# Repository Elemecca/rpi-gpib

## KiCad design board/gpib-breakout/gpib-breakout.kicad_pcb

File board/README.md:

## Copying

Copyright 2019 Sam Hanes

This documentation describes Open Hardware and is licensed under
the CERN Open Hardware License v1.2.

You may redistribute and modify this documentation under the terms of
the CERN OHL v1.2. (http://ohwr.org/cernohl). This documentation is
distributed WITHOUT ANY EXPRESS OR IMPLIED WARRANTY, INCLUDING OF
MERCHANTABILITY, SATISFACTORY QUALITY AND FITNESS FOR APARTICULAR
PURPOSE. Please see the CERN OHL v1.2 for applicable conditions

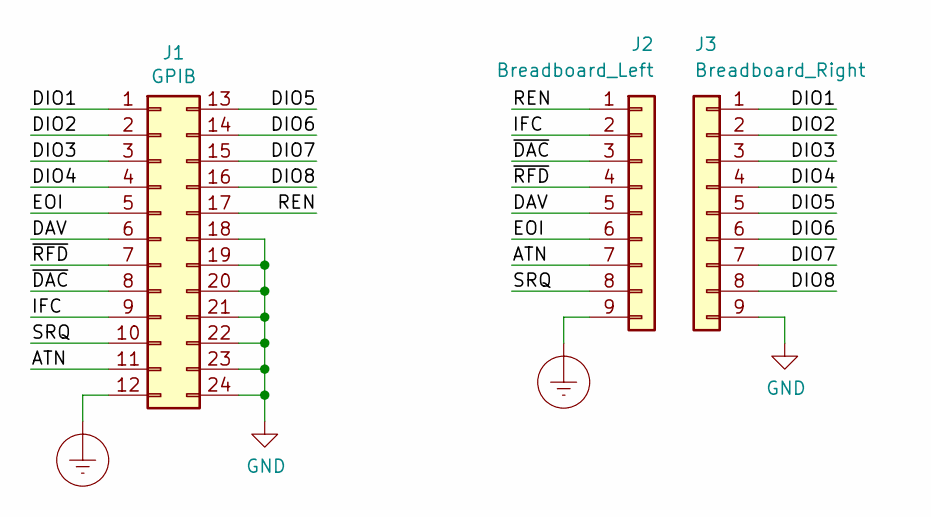
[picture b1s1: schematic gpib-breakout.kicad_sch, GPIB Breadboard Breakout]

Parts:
J1: GPIB; NorComp_111-024-213L001
J2: Breadboard_Left; PinHeader_1x09_P2.54mm_Vertical
J3: Breadboard_Right; PinHeader_1x09_P2.54mm_Vertical

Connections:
/ATN: J1.11, J2.7
/DAV: J1.6, J2.5
/DIO1: J1.1, J3.1
/DIO2: J1.2, J3.2
/DIO3: J1.3, J3.3
/DIO4: J1.4, J3.4
/DIO5: J1.13, J3.5
/DIO6: J1.14, J3.6
/DIO7: J1.15, J3.7
/DIO8: J1.16, J3.8
/EOI: J1.5, J2.6
/IFC: J1.9, J2.2
/REN: J1.17, J2.1
/SRQ: J1.10, J2.8
/~DAC: J1.8, J2.3
/~RFD: J1.7, J2.4
Earth_Protective: J1.12, J2.9
GND: J1.18, J1.19, J1.20, J1.21, J1.22, J1.23, J1.24, J3.9

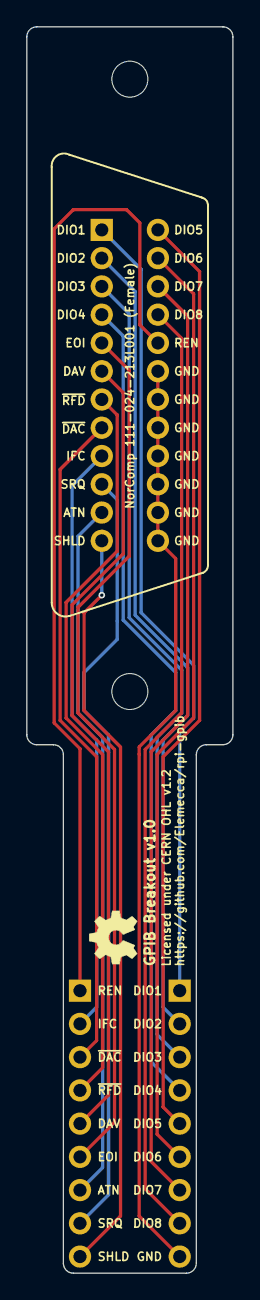
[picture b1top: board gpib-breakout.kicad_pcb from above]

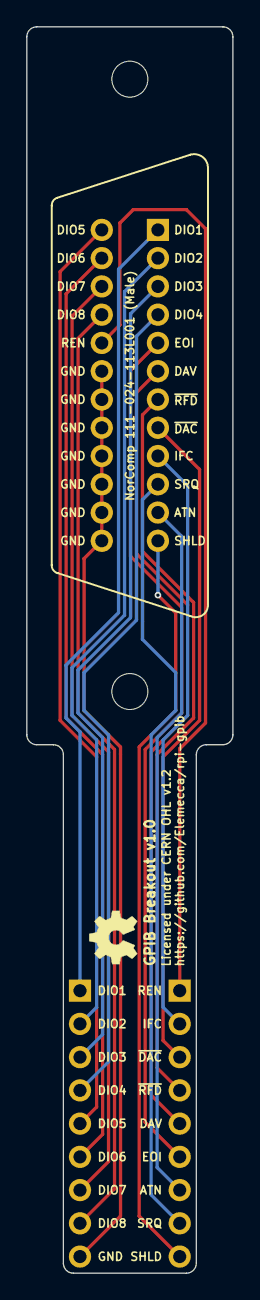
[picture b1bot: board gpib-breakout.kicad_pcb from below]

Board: 2 copper layers, 15.7 x 95.2 mm, 5 parts (3 on the bottom side), 18 nets.

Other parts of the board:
OSHW: LOGO; OSHW
OSHW#2: LOGO; OSHW

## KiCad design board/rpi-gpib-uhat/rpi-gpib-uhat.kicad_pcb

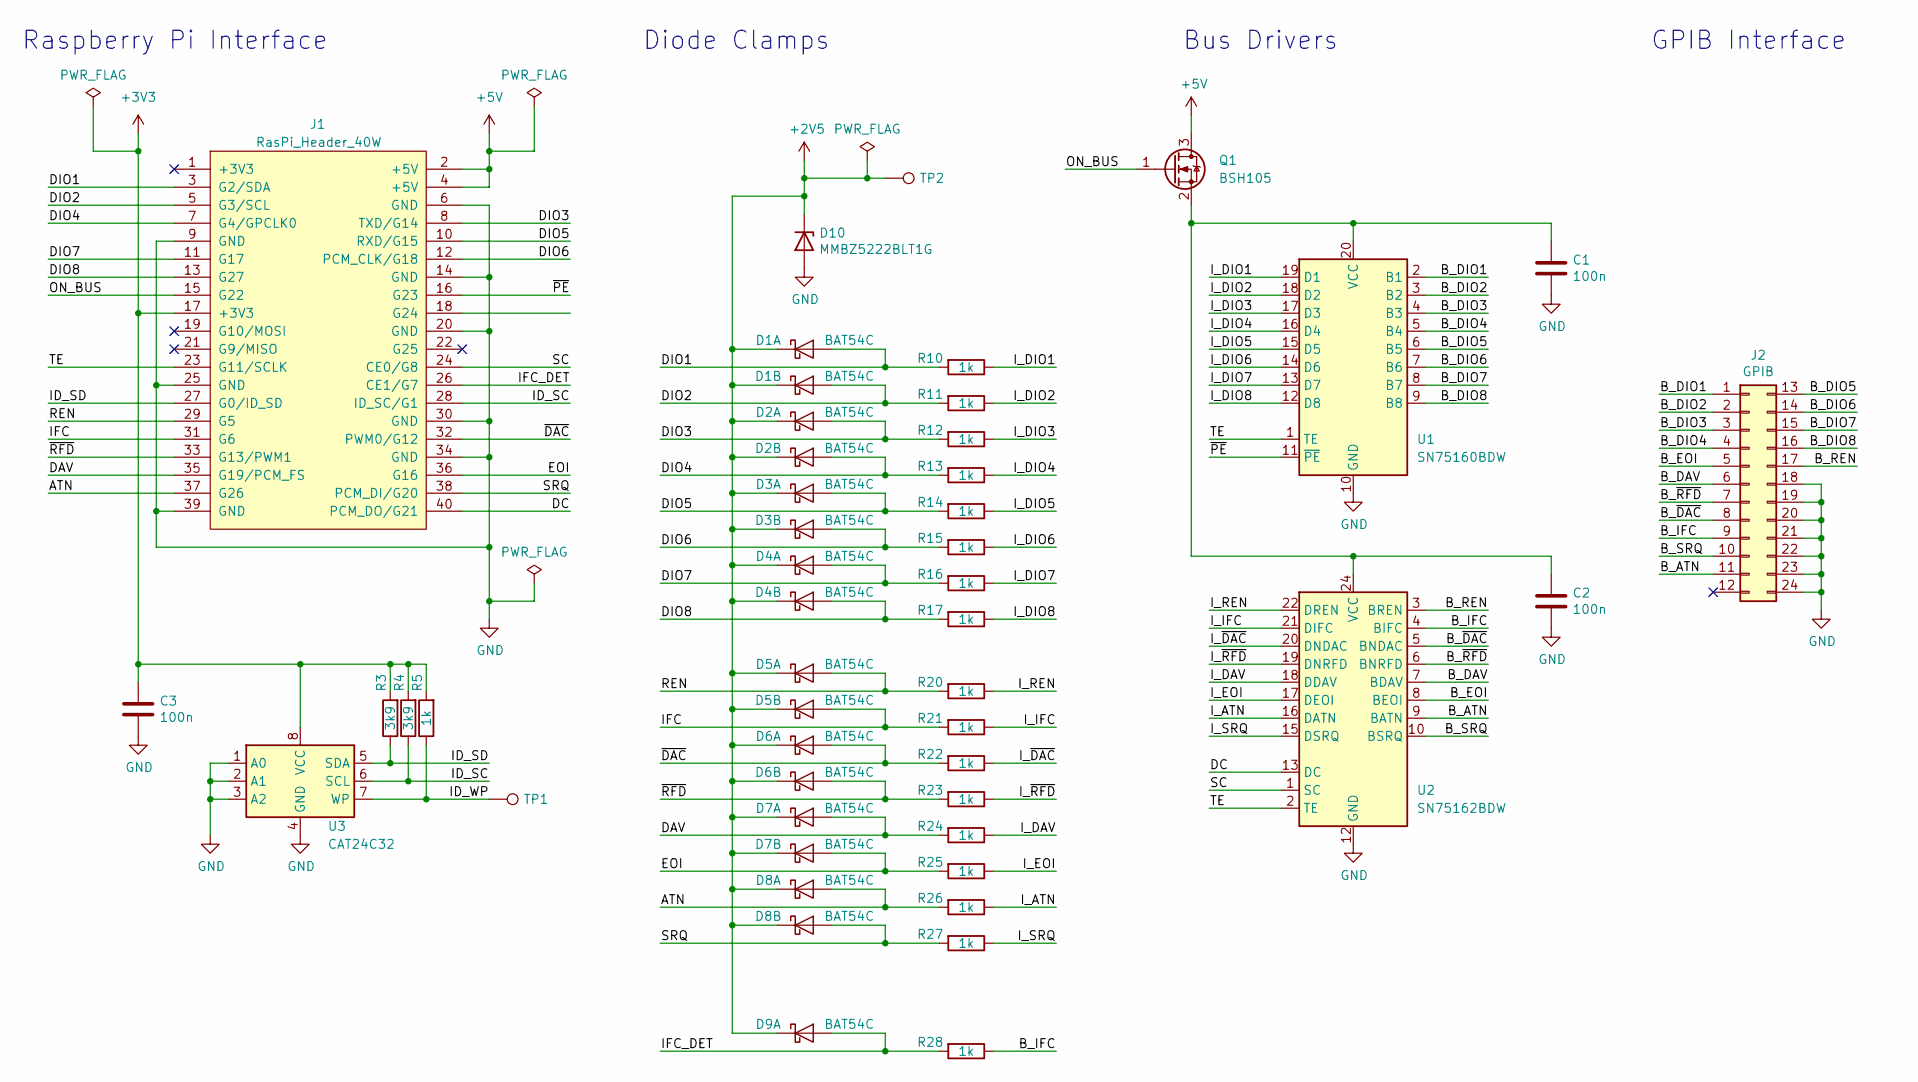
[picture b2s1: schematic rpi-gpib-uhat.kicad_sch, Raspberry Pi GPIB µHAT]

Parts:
C1, C2, C3: 100n; C_0402_1005Metric
D1, D2, D3, D4, D5, D6, D7, D8, D9: BAT54C; SOT-23
D10: MMBZ5222BLT1G; SC-59
J1: RasPi_Header_40W; PinSocket_2x20_P2.54mm_Vertical_Centered_Anchor
J2: GPIB; NorComp_111-024-113L001_NoScrews
Q1: BSH105; SOT-23
R3, R4: 3k9; R_0402_1005Metric
R5, R10, R11, R12, R13, R14, R15, R16, R17, R20, R21, R22, R23, R24, R25, R26, R27, R28: 1k; R_0402_1005Metric
TP1, TP2: TestPoint; TestPoint_Pad_D1.0mm
U1: SN75160BDW; SOIC-20W_7.5x12.8mm_P1.27mm
U2: SN75162BDW; SOIC-24W_7.5x15.4mm_P1.27mm
U3: CAT24C32; SOIC-8_3.9x4.9mm_P1.27mm

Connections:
+2V5: D1.3 (K), D2.3 (K), D3.3 (K), D4.3 (K), D5.3 (K), D6.3 (K), D7.3 (K), D8.3 (K), D9.3 (K), D10.1 (K), TP2.1
+3V3: C3.1, J1.17 (+3V3), R3.2, R4.2, R5.2, U3.8 (VCC)
+5V: J1.2 (+5V), J1.4 (+5V), Q1.3 (D)
/ATN: D8.1 (A), J1.37 (G26), R26.2
/B_ATN: J2.11, U2.9 (BATN)
/B_DAV: J2.6, U2.7 (BDAV)
/B_DIO1: J2.1, U1.2 (B1)
/B_DIO2: J2.2, U1.3 (B2)
/B_DIO3: J2.3, U1.4 (B3)
/B_DIO4: J2.4, U1.5 (B4)
/B_DIO5: J2.13, U1.6 (B5)
/B_DIO6: J2.14, U1.7 (B6)
/B_DIO7: J2.15, U1.8 (B7)
/B_DIO8: J2.16, U1.9 (B8)
/B_EOI: J2.5, U2.8 (BEOI)
/B_IFC: J2.9, R28.1, U2.4 (BIFC)
/B_REN: J2.17, U2.3 (BREN)
/B_SRQ: J2.10, U2.10 (BSRQ)
/B_~DAC: J2.8, U2.5 (BNDAC)
/B_~RFD: J2.7, U2.6 (BNRFD)
/DAV: D7.1 (A), J1.35 (G19/PCM_FS), R24.2
/DC: J1.40 (PCM_DO/G21), U2.13 (DC)
/DIO1: D1.1 (A), J1.3 (G2/SDA), R10.2
/DIO2: D1.2 (A), J1.5 (G3/SCL), R11.2
/DIO3: D2.1 (A), J1.8 (TXD/G14), R12.2
/DIO4: D2.2 (A), J1.7 (G4/GPCLK0), R13.2
/DIO5: D3.1 (A), J1.10 (RXD/G15), R14.2
/DIO6: D3.2 (A), J1.12 (PCM_CLK/G18), R15.2
/DIO7: D4.1 (A), J1.11 (G17), R16.2
/DIO8: D4.2 (A), J1.13 (G27), R17.2
/EOI: D7.2 (A), J1.36 (G16), R25.2
/ID_SC: J1.28 (ID_SC/G1), R4.1, U3.6 (SCL)
/ID_SD: J1.27 (G0/ID_SD), R3.1, U3.5 (SDA)
/ID_WP: R5.1, TP1.1, U3.7 (WP)
/IFC: D5.2 (A), J1.31 (G6), R21.2
/IFC_DET: D9.1 (A), J1.26 (CE1/G7), R28.2
/I_ATN: R26.1, U2.16 (DATN)
/I_DAV: R24.1, U2.18 (DDAV)
/I_DIO1: R10.1, U1.19 (D1)
/I_DIO2: R11.1, U1.18 (D2)
/I_DIO3: R12.1, U1.17 (D3)
/I_DIO4: R13.1, U1.16 (D4)
/I_DIO5: R14.1, U1.15 (D5)
/I_DIO6: R15.1, U1.14 (D6)
/I_DIO7: R16.1, U1.13 (D7)
/I_DIO8: R17.1, U1.12 (D8)
/I_EOI: R25.1, U2.17 (DEOI)
/I_IFC: R21.1, U2.21 (DIFC)
/I_REN: R20.1, U2.22 (DREN)
/I_SRQ: R27.1, U2.15 (DSRQ)
/I_~DAC: R22.1, U2.20 (DNDAC)
/I_~RFD: R23.1, U2.19 (DNRFD)
/ON_BUS: J1.15 (G22), Q1.1 (G)
/REN: D5.1 (A), J1.29 (G5), R20.2
/SC: J1.24 (CE0/G8), U2.1 (SC)
/SRQ: D8.2 (A), J1.38 (PCM_DI/G20), R27.2
/TE: J1.23 (G11/SCLK), U1.1 (TE), U2.2 (TE)
/~DAC: D6.1 (A), J1.32 (PWM0/G12), R22.2
/~PE: J1.16 (G23), U1.11 (~PE)
/~RFD: D6.2 (A), J1.33 (G13/PWM1), R23.2
GND: C1.2, C2.2, C3.2, D10.2 (A), J1.6 (GND), J1.9 (GND), J1.14 (GND), J1.20 (GND), J1.25 (GND), J1.30 (GND), J1.34 (GND), J1.39 (GND), J2.18, J2.19, J2.20, J2.21, J2.22, J2.23, J2.24, U1.10 (GND), U2.12 (GND), U3.1 (A0), U3.2 (A1), U3.3 (A2), U3.4 (GND)
unnamed: C1.1, C2.1, Q1.2 (S), U1.20 (VCC), U2.24 (VCC)

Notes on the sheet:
Bus Drivers
Raspberry Pi Interface
Diode Clamps
GPIB Interface

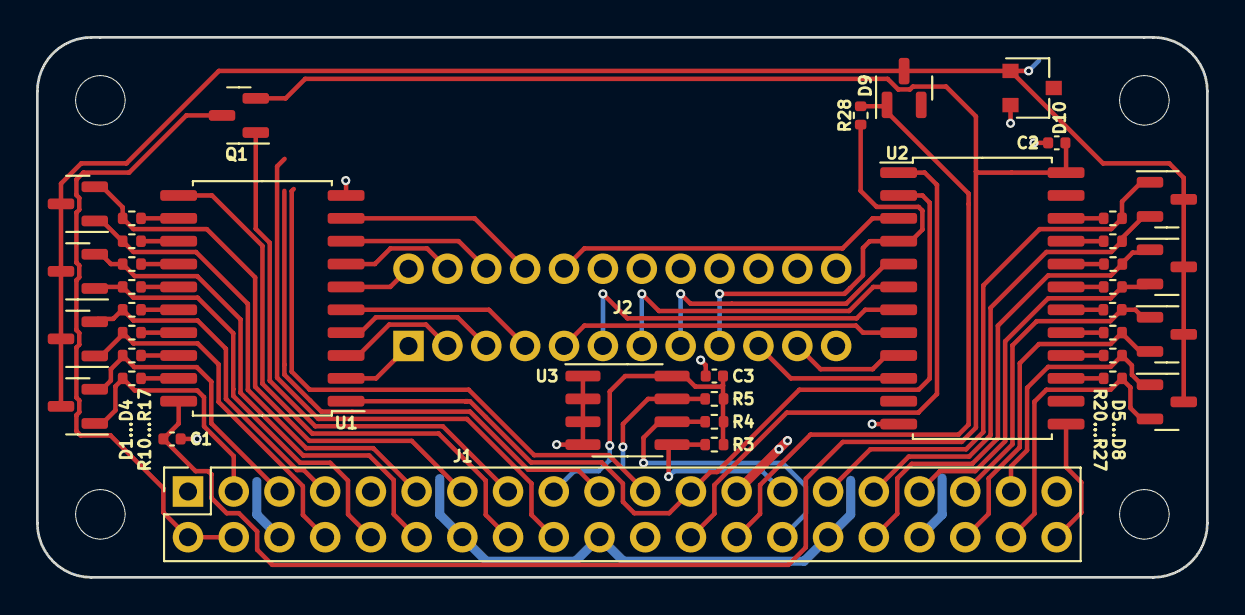
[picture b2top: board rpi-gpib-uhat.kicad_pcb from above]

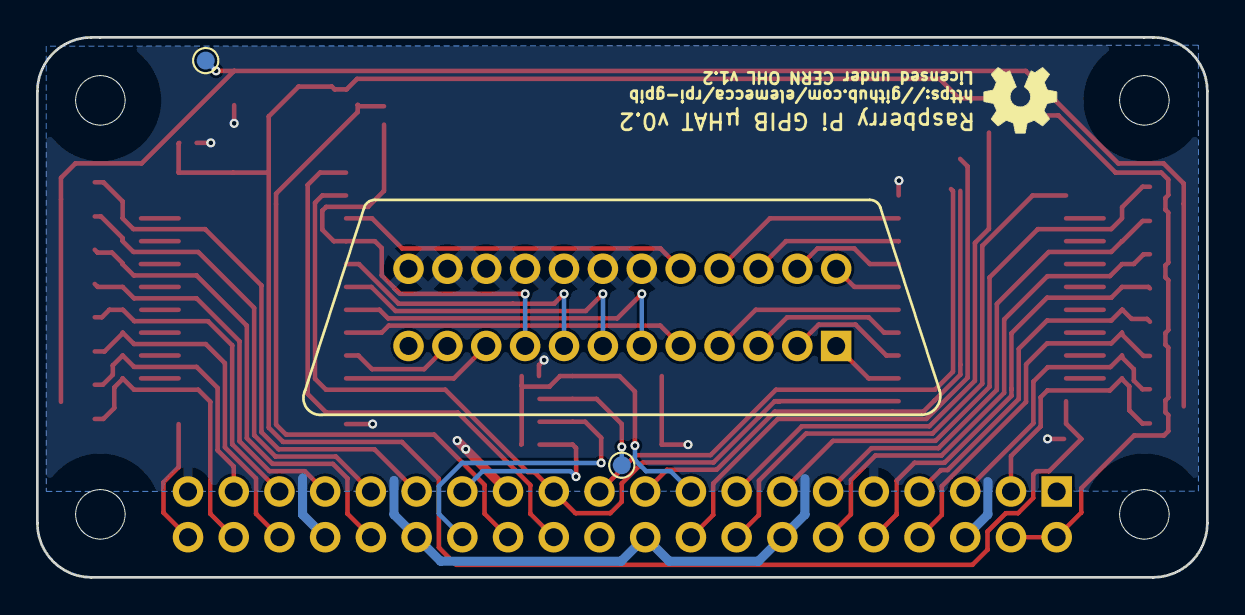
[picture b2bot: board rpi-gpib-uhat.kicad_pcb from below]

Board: 2 copper layers, 65.0 x 30.0 mm, 46 parts (4 on the bottom side), 62 nets.

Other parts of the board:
H1, H2, H3, H4: MountingHole; MountingHole_RPi_HAT
OSHW: LOGO; OSHW

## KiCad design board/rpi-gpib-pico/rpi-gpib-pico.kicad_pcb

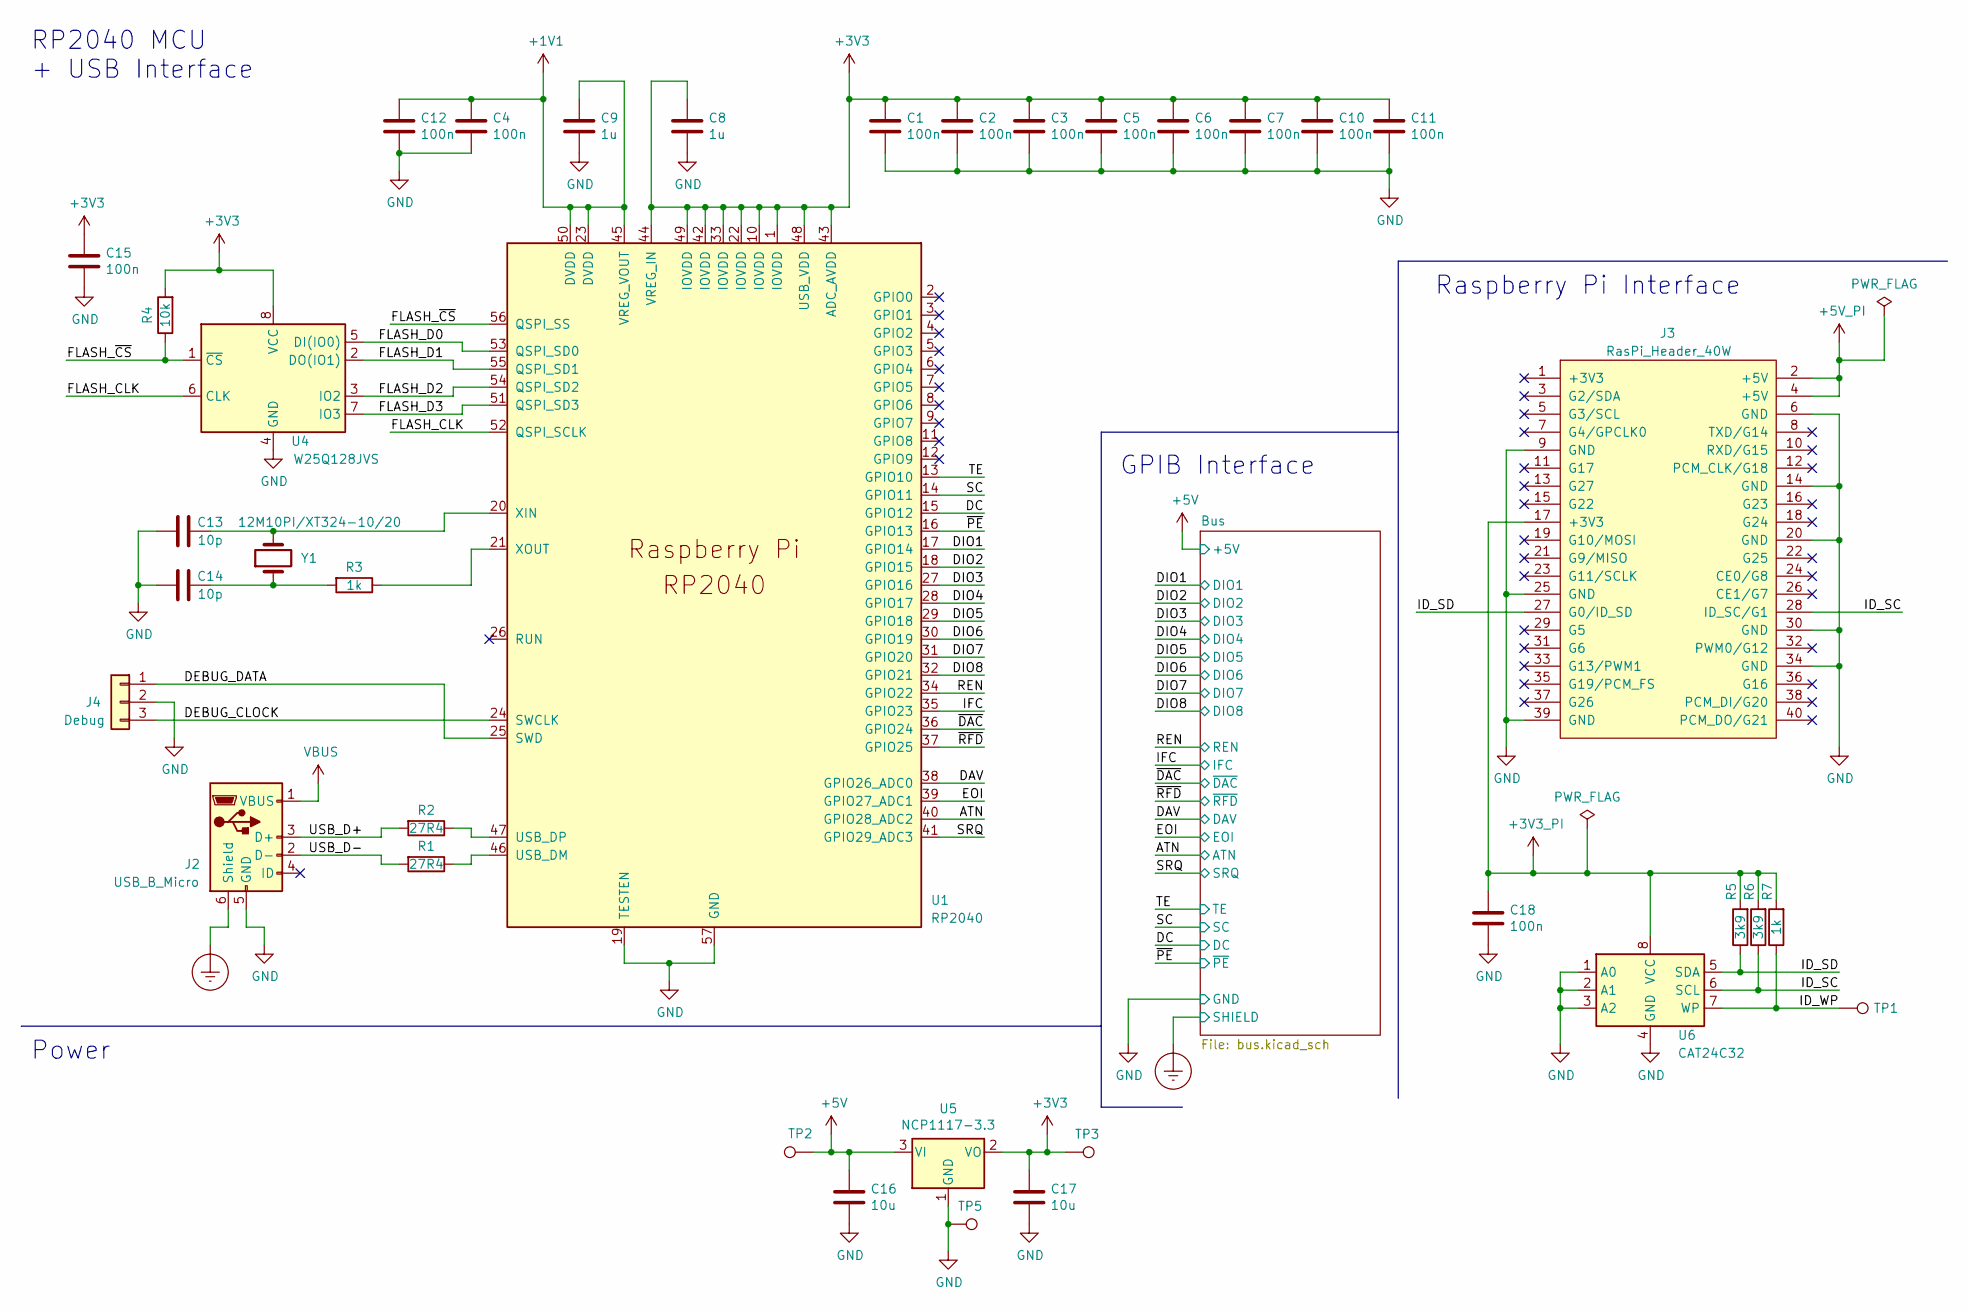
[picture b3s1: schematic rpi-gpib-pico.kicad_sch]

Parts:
C1, C2, C3, C4, C5, C6, C7, C10, C11, C12, C15, C18: 100n; C_0402_1005Metric
C8, C9: 1u; C_0402_1005Metric
C13, C14: 10p; C_0402_1005Metric
C16, C17: 10u; C_0402_1005Metric
J2: USB_B_Micro; USB_Micro-B_Amphenol_10118194_Horizontal
J3: RasPi_Header_40W; PinSocket_2x20_P2.54mm_Vertical_Centered_Anchor
J4: Debug; PinHeader_1x03_P2.54mm_Vertical
R1, R2: 27R4; R_0402_1005Metric
R3, R7: 1k; R_0402_1005Metric
R4: 10k; R_0402_1005Metric
R5, R6: 3k9; R_0402_1005Metric
TP1, TP2, TP3, TP5: TestPoint; TestPoint_Pad_D1.0mm
U1: RP2040; RP2040-QFN-56
U4: W25Q128JVS; SOIC-8_5.23x5.23mm_P1.27mm
U5: NCP1117-3.3; SOT-223-3_TabPin2
U6: CAT24C32; SOIC-8_3.9x4.9mm_P1.27mm
Y1: 12M10PI/XT324-10/20; Crystal_SMD_3225-4Pin_3.2x2.5mm

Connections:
+1V1: C4.1, C9.1, C12.1, U1.23 (DVDD), U1.45 (VREG_VOUT), U1.50 (DVDD)
+3V3: C1.1, C2.1, C3.1, C5.1, C6.1, C7.1, C8.1, C10.1, C11.1, C15.1, C17.1, R4.2, TP3.1, U1.1 (IOVDD), U1.10 (IOVDD), U1.22 (IOVDD), U1.33 (IOVDD), U1.42 (IOVDD), U1.43 (ADC_AVDD), U1.44 (VREG_IN), U1.48 (USB_VDD), U1.49 (IOVDD), U4.8 (VCC), U5.2 (VO)
+3V3_PI: C18.1, J3.17 (+3V3), R5.2, R6.2, R7.2, U6.8 (VCC)
+5V: C16.1, TP2.1, U5.3 (VI); also elsewhere on the board
+5V_PI: J3.2 (+5V), J3.4 (+5V)
/ATN: U1.40 (GPIO28_ADC2); also elsewhere on the board
/DAV: U1.38 (GPIO26_ADC0); also elsewhere on the board
/DC: U1.15 (GPIO12); also elsewhere on the board
/DEBUG_CLOCK: J4.3, U1.24 (SWCLK)
/DEBUG_DATA: J4.1, U1.25 (SWD)
/DIO1: U1.17 (GPIO14); also elsewhere on the board
/DIO2: U1.18 (GPIO15); also elsewhere on the board
/DIO3: U1.27 (GPIO16); also elsewhere on the board
/DIO4: U1.28 (GPIO17); also elsewhere on the board
/DIO5: U1.29 (GPIO18); also elsewhere on the board
/DIO6: U1.30 (GPIO19); also elsewhere on the board
/DIO7: U1.31 (GPIO20); also elsewhere on the board
/DIO8: U1.32 (GPIO21); also elsewhere on the board
/EOI: U1.39 (GPIO27_ADC1); also elsewhere on the board
/FLASH_CLK: U1.52 (QSPI_SCLK), U4.6 (CLK)
/FLASH_D0: U1.53 (QSPI_SD0), U4.5 (DI(IO0))
/FLASH_D1: U1.55 (QSPI_SD1), U4.2 (DO(IO1))
/FLASH_D2: U1.54 (QSPI_SD2), U4.3 (IO2)
/FLASH_D3: U1.51 (QSPI_SD3), U4.7 (IO3)
/FLASH_~CS: R4.1, U1.56 (QSPI_SS), U4.1 (~CS)
/ID_SC: J3.28 (ID_SC/G1), R6.1, U6.6 (SCL)
/ID_SD: J3.27 (G0/ID_SD), R5.1, U6.5 (SDA)
/ID_WP: R7.1, TP1.1, U6.7 (WP)
/IFC: U1.35 (GPIO23); also elsewhere on the board
/REN: U1.34 (GPIO22); also elsewhere on the board
/SC: U1.14 (GPIO11); also elsewhere on the board
/SRQ: U1.41 (GPIO29_ADC3); also elsewhere on the board
/TE: U1.13 (GPIO10); also elsewhere on the board
/USB_D+: J2.3 (D+), R2.2
/USB_D-: J2.2 (D-), R1.2
/~DAC: U1.36 (GPIO24); also elsewhere on the board
/~PE: U1.16 (GPIO13); also elsewhere on the board
/~RFD: U1.37 (GPIO25); also elsewhere on the board
Earth_Protective: J2.6 (Shield); also elsewhere on the board
GND: C1.2, C2.2, C3.2, C4.2, C5.2, C6.2, C7.2, C8.2, C9.2, C10.2, C11.2, C12.2, C13.2, C14.2, C15.2, C16.2, C17.2, C18.2, J2.5 (GND), J3.6 (GND), J3.9 (GND), J3.14 (GND), J3.20 (GND), J3.25 (GND), J3.30 (GND), J3.34 (GND), J3.39 (GND), J4.2, TP5.1, U1.19 (TESTEN), U1.57 (GND), U4.4 (GND), U5.1 (GND), U6.1 (A0), U6.2 (A1), U6.3 (A2), U6.4 (GND); also elsewhere on the board
unnamed: C13.1, U1.20 (XIN), Y1.2
unnamed: C14.1, R3.2, Y1.1
unnamed: R1.1, U1.46 (USB_DM)
unnamed: R2.1, U1.47 (USB_DP)
unnamed: R3.1, U1.21 (XOUT)
VBUS: J2.1 (VBUS)

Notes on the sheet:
GPIB Interface
Power
RP2040 MCU + USB Interface
Raspberry Pi Interface

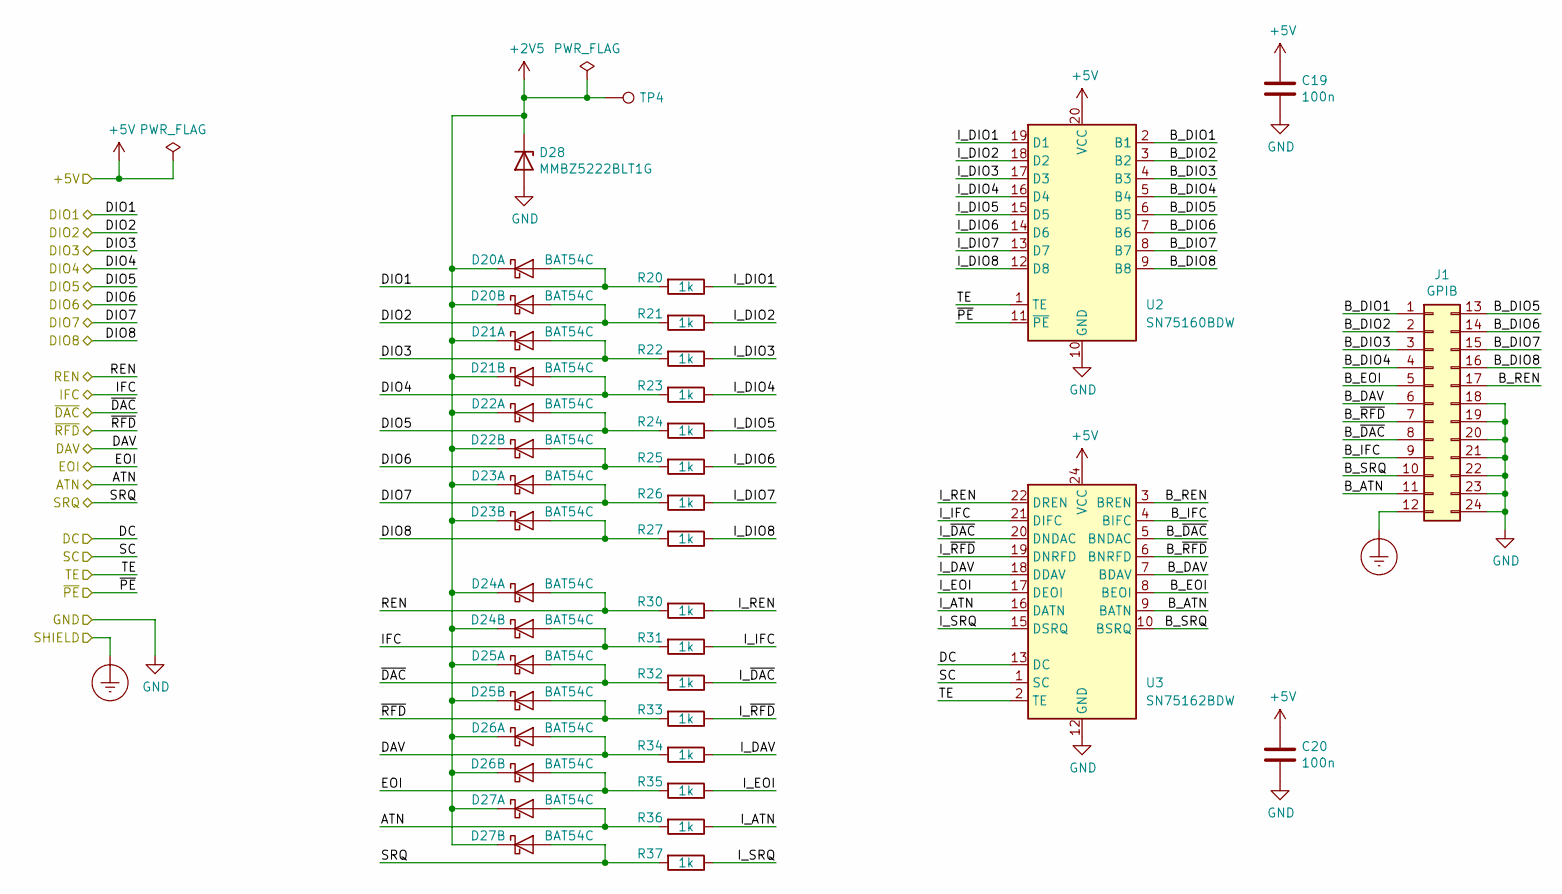
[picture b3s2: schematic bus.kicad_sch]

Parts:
C19, C20: 100n; C_0402_1005Metric
D20, D21, D22, D23, D24, D25, D26, D27: BAT54C; SOT-23
D28: MMBZ5222BLT1G; SC-59
J1: GPIB; NorComp_112-024-113R001
R20, R21, R22, R23, R24, R25, R26, R27, R30, R31, R32, R33, R34, R35, R36, R37: 1k; R_0402_1005Metric
TP4: TestPoint; TestPoint_Pad_D1.0mm
U2: SN75160BDW; SOIC-20W_7.5x12.8mm_P1.27mm
U3: SN75162BDW; SOIC-24W_7.5x15.4mm_P1.27mm

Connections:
+2V5: D20.3 (K), D21.3 (K), D22.3 (K), D23.3 (K), D24.3 (K), D25.3 (K), D26.3 (K), D27.3 (K), D28.1 (K), TP4.1
+5V: C19.1, C20.1, U2.20 (VCC), U3.24 (VCC); also elsewhere on the board
/ATN: D27.1 (A), R36.2; also elsewhere on the board
/Bus/B_ATN: J1.11, U3.9 (BATN)
/Bus/B_DAV: J1.6, U3.7 (BDAV)
/Bus/B_DIO1: J1.1, U2.2 (B1)
/Bus/B_DIO2: J1.2, U2.3 (B2)
/Bus/B_DIO3: J1.3, U2.4 (B3)
/Bus/B_DIO4: J1.4, U2.5 (B4)
/Bus/B_DIO5: J1.13, U2.6 (B5)
/Bus/B_DIO6: J1.14, U2.7 (B6)
/Bus/B_DIO7: J1.15, U2.8 (B7)
/Bus/B_DIO8: J1.16, U2.9 (B8)
/Bus/B_EOI: J1.5, U3.8 (BEOI)
/Bus/B_IFC: J1.9, U3.4 (BIFC)
/Bus/B_REN: J1.17, U3.3 (BREN)
/Bus/B_SRQ: J1.10, U3.10 (BSRQ)
/Bus/B_~DAC: J1.8, U3.5 (BNDAC)
/Bus/B_~RFD: J1.7, U3.6 (BNRFD)
/Bus/I_ATN: R36.1, U3.16 (DATN)
/Bus/I_DAV: R34.1, U3.18 (DDAV)
/Bus/I_DIO1: R20.1, U2.19 (D1)
/Bus/I_DIO2: R21.1, U2.18 (D2)
/Bus/I_DIO3: R22.1, U2.17 (D3)
/Bus/I_DIO4: R23.1, U2.16 (D4)
/Bus/I_DIO5: R24.1, U2.15 (D5)
/Bus/I_DIO6: R25.1, U2.14 (D6)
/Bus/I_DIO7: R26.1, U2.13 (D7)
/Bus/I_DIO8: R27.1, U2.12 (D8)
/Bus/I_EOI: R35.1, U3.17 (DEOI)
/Bus/I_IFC: R31.1, U3.21 (DIFC)
/Bus/I_REN: R30.1, U3.22 (DREN)
/Bus/I_SRQ: R37.1, U3.15 (DSRQ)
/Bus/I_~DAC: R32.1, U3.20 (DNDAC)
/Bus/I_~RFD: R33.1, U3.19 (DNRFD)
/DAV: D26.1 (A), R34.2; also elsewhere on the board
/DC: U3.13 (DC); also elsewhere on the board
/DIO1: D20.1 (A), R20.2; also elsewhere on the board
/DIO2: D20.2 (A), R21.2; also elsewhere on the board
/DIO3: D21.1 (A), R22.2; also elsewhere on the board
/DIO4: D21.2 (A), R23.2; also elsewhere on the board
/DIO5: D22.1 (A), R24.2; also elsewhere on the board
/DIO6: D22.2 (A), R25.2; also elsewhere on the board
/DIO7: D23.1 (A), R26.2; also elsewhere on the board
/DIO8: D23.2 (A), R27.2; also elsewhere on the board
/EOI: D26.2 (A), R35.2; also elsewhere on the board
/IFC: D24.2 (A), R31.2; also elsewhere on the board
/REN: D24.1 (A), R30.2; also elsewhere on the board
/SC: U3.1 (SC); also elsewhere on the board
/SRQ: D27.2 (A), R37.2; also elsewhere on the board
/TE: U2.1 (TE), U3.2 (TE); also elsewhere on the board
/~DAC: D25.1 (A), R32.2; also elsewhere on the board
/~PE: U2.11 (~PE); also elsewhere on the board
/~RFD: D25.2 (A), R33.2; also elsewhere on the board
Earth_Protective: J1.12; also elsewhere on the board
GND: C19.2, C20.2, D28.2 (A), J1.18, J1.19, J1.20, J1.21, J1.22, J1.23, J1.24, U2.10 (GND), U3.12 (GND); also elsewhere on the board

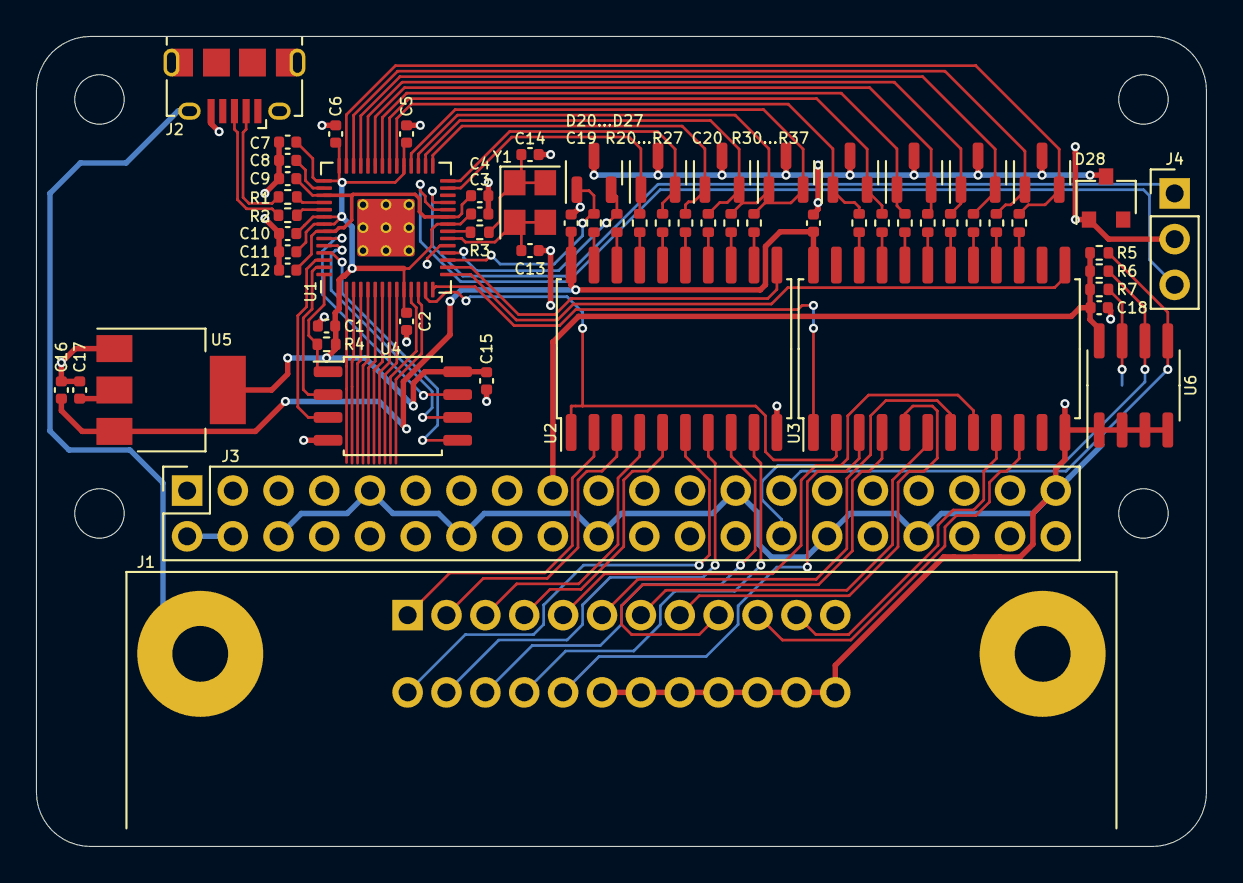
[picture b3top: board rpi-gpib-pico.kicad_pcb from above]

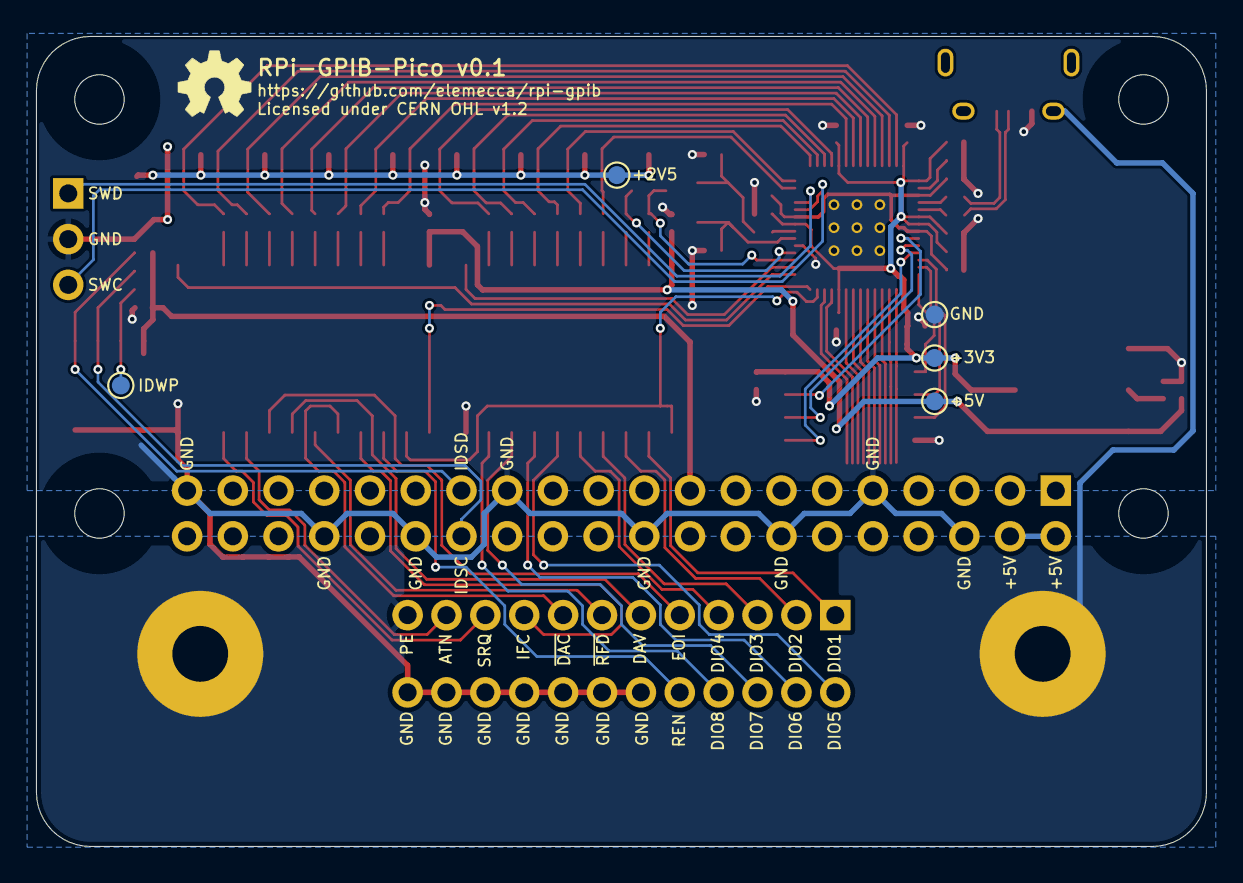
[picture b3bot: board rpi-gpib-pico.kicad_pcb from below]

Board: 2 copper layers, 65.0 x 45.0 mm, 73 parts (6 on the bottom side), 78 nets.

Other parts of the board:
H1, H1#2, H1#3, H2: MountingHole; MountingHole_RPi_HAT
OSHW: LOGO; OSHW

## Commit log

2019-05-16 Start board layout with outline and connectors.
2019-05-16 Add project imprint and OSHW logo to board.
2019-05-16 Fix mounting holes to meet uHat spec.
2019-05-16 Add courtyard for POE header.
2019-05-16 Add mounting holes for GPIB connector.
2019-05-16 Realign PCB to the millimeter grid.
2019-05-16 Fix NPTH size to match uHAT spec.
2019-05-16 Set up for Gerber output.
2019-05-16 Remove ground fills for now.
    They're just in the way and there probably wont' be room for them.
2019-05-18 Add GPIB transceivers and ident EEPROM.
2019-05-18 Start laying out the PCB.
2019-05-18 Finish routing terminal-side GPIB lines.
2019-05-18 Route data bus terminators.
2019-05-18 Route control bus terminations.
2019-05-18 Route the rest of the board.
2019-05-18 Misc routing cleanup.
2019-05-18 Add reference designators.
2019-05-21 License hardware under CERN OHL v1.2.
2022-01-23 Add 2.5V regulator for diode clamps.
2022-01-23 Clean up routing.
2022-01-28 Create board for RP2040-based interface.
2022-01-28 Swap connectors to top of pico board.
2022-01-29 Place and route most of the pico board.
2022-01-30 Rotate RP2040 to fit in crystal.
2022-01-30 Route more stuff.
2022-01-30 Route almost everything.
2022-01-30 Add labels and test points.
2022-01-31 Renumber caps to make more sense.
2022-02-02 Set up hello world pico firmware.
2022-02-02 Add PIO program to test max bus rate.
2022-02-05 Clean up pico schematic.
2022-02-06 Move ID EEPROM to RPI 3V3 supply.
2022-02-16 Rename board projects and convert to KiCAD 6.
2022-02-17 Change uHAT pinout and re-route.
2022-02-24 Add FET switch for bus drivers.
2022-02-26 Add GPIB connector breakout board.

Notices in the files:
board/gpib-breakout/gpib-breakout.kicad_pcb:
© 2022 Sam Hanes. Licensed under CERN OHL v1.2.
board/rpi-gpib-uhat/rpi-gpib-uhat.kicad_pcb:
© 2019 Sam Hanes. Licensed under CERN OHL v1.2.
